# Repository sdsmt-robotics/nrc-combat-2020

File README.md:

# nrc-combat-2020
Robot code for the NRC Combat competition bot. Information about this bot can be found here: http://robotics.sdsmt.edu/projects/spinnybot  

# Hardware Info
This code is meant to run on an ESP32. It uses an ICM20649 Wide-Range 6-DoF IMU for orientation sensing. It also controls three NeoPixel 8x5050 RGB LED Sticks. For motor control, it interfaces with three Nidec24h motors controlled by our custom motor controller boards. For remote control, the bot receives commands from our custom remote controls over an xBee. The full system diagram is shown below.  

The main components of the control system (ESP32, xBee, voltage regulators, level shifters, etc) are held on a custom main board. The Kicad files for this are in the [spinnybot-motherboard](https://github.com/sdsmt-robotics/nrc-combat-2020/tree/master/spinnybot-motherboad) folder.  

# Software Info  
The main code for the bot is found in the [spinnybot-code](https://github.com/sdsmt-robotics/nrc-combat-2020/tree/master/spinnybot-code) folder. There are some additional arduino sketches for testing the various functionallities. These are found in the "testing" sub-folder. These tests run with the same libraries as the main control code.  

The pinouts are set up to run with the ESP32. But it should be able to run on any device with similar pin functionalities.  

## Required Libraries  
The required libraries are as follows:  
* Nidec24hController.h - Interface lib for the motor speed controller. Found [here](https://github.com/sdsmt-robotics/MotorSpeedController/tree/master/Software/controllerInterfaceLib).  
* Controller.h - Receive library for our custom remote control. Found [here](https://github.com/sdsmt-robotics/MotorSpeedController/tree/master/Software/controllerInterfaceLib).  
* FastLED.h - Code for interfacing with the LED strips. Install through the Arduino library manager.  
* Adafruit_ICM20649.h - Library for the ICM-20649 IMU. Install through the Arduino library manager.  

## Functionality  
The functionality is as follows. First, the bot will first initialize all peripherals. The LED strips are initialized first to show status throughout.Then the IMU is initialized. While this is occurring, the bot MUST remain stationary. The code runs through a calibration sequence each time, and any bumps will cause issues. During this stage the LEDs will show yellow, and will go green once complete. After, this the motors and remote control communications will be set up as well.  

For the main control loop, the bot has three main states:  
* No-spin: lights will be purple and the bot will not be spinning. Driver can drive the bot around with standard controls.  
* Spinny: bot is spinning with IMU feedback for orientation. LEDs will be red except when facing forward at which point they will be blue. Controls for driving are relative to "forward".  
* Full-spinny: lights will be red and bot will set all motors to full power. Feedback from IMU and attempts to drive will be ignored.

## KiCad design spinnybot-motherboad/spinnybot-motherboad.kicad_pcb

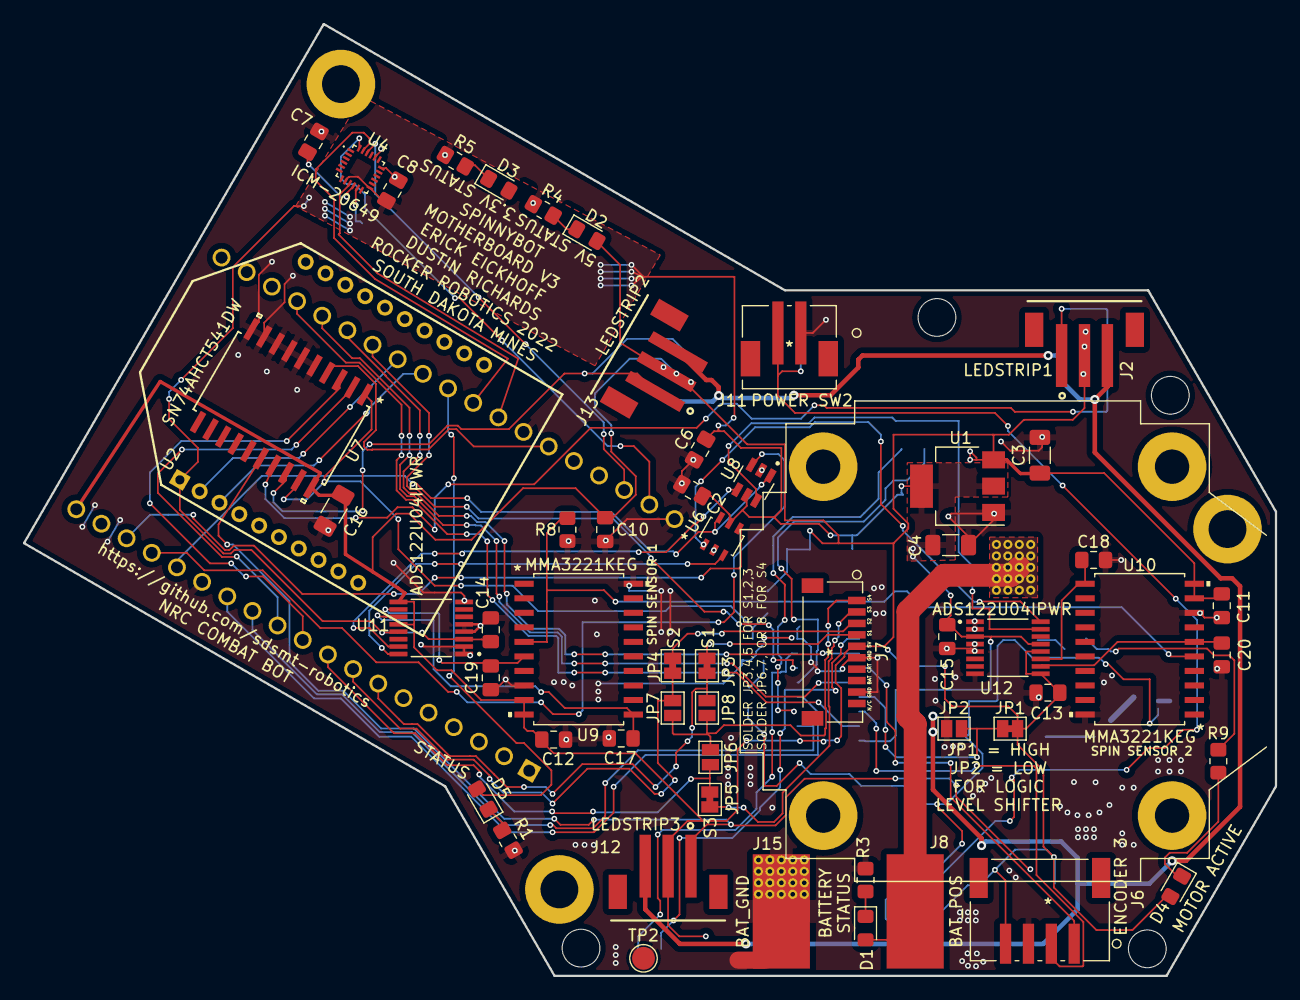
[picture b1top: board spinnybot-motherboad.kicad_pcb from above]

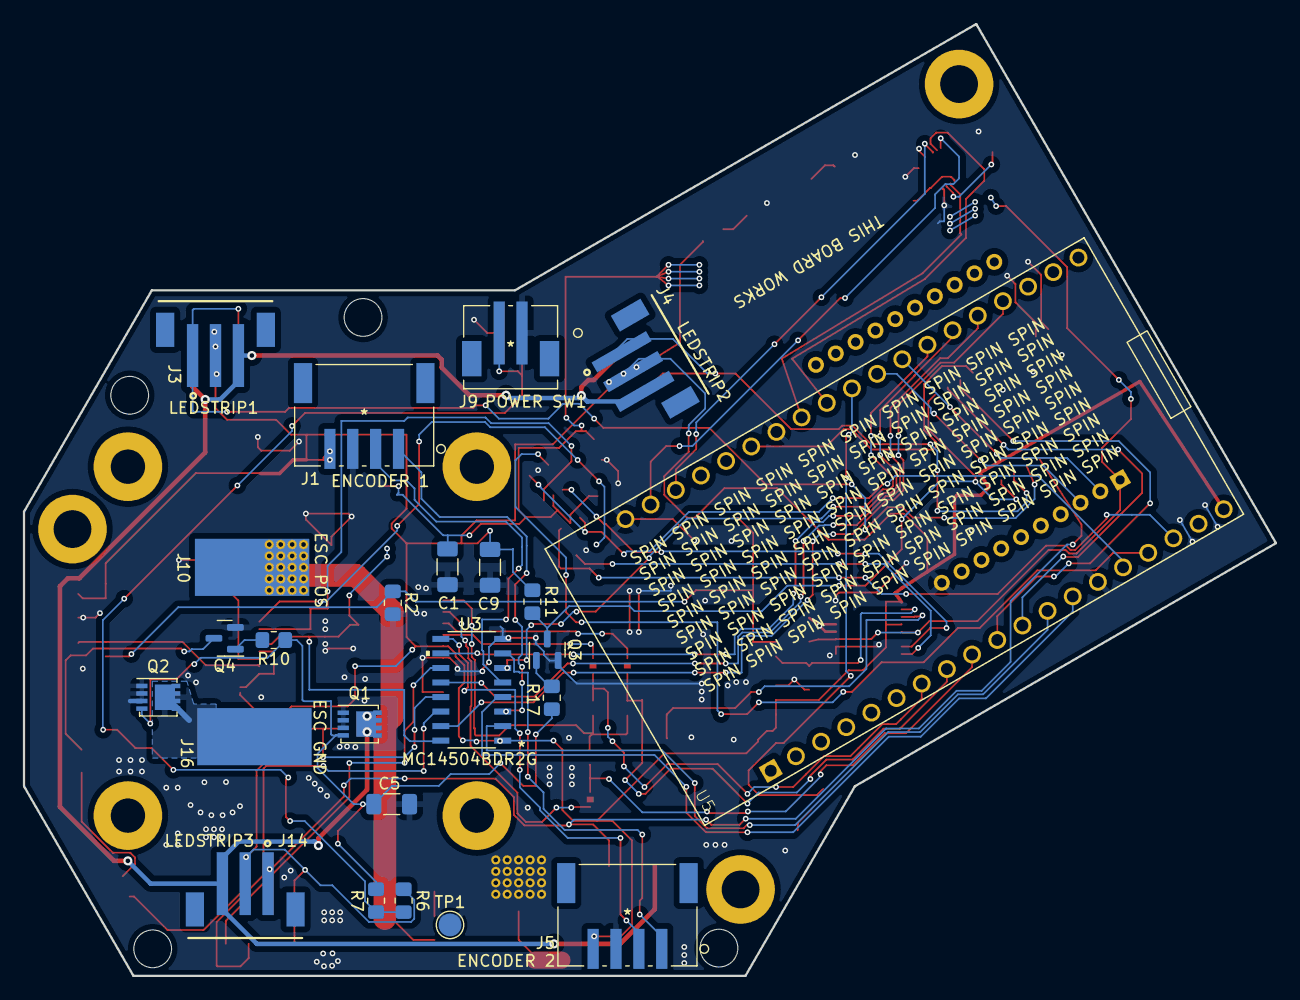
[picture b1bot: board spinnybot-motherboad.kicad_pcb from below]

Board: 2 copper layers, 109.4 x 83.2 mm, 87 parts (24 on the bottom side), 63 nets.

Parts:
A1: ESC_Hobbywing_X-Rotor_Micro_60A_4in1
C1, C3, C4, C5, C9: 10u; C_1206_3216Metric_Pad1.33x1.80mm_HandSolder
C2, C6, C7, C8, C10, C11, C12, C13, C14, C15: 0.1u; C_0805_2012Metric_Pad1.18x1.45mm_HandSolder
C16: 0.1u; C_1206_3216Metric_Pad1.33x1.80mm_HandSolder
C17, C18, C19, C20: 10nF; C_0805_2012Metric_Pad1.18x1.45mm_HandSolder
D1: 12V; LED_0805_2012Metric_Pad1.15x1.40mm_HandSolder
D2: 5V; LED_0805_2012Metric_Pad1.15x1.40mm_HandSolder
D3: 3V3; LED_0805_2012Metric_Pad1.15x1.40mm_HandSolder
D4: MOTOR ACTIVE; LED_0805_2012Metric_Pad1.15x1.40mm_HandSolder
D5: STATUS; LED_0805_2012Metric_Pad1.15x1.40mm_HandSolder
H1: MOUNTINGHOLE1; MountingHole_3.3mm
H2, H7: STRAINHOLE1; StrainHole_3.3mm
H3: MOUNTINGHOLE2; MountingHole_3.3mm
H4: MOUNTINGHOLE3; MountingHole_3.3mm
H6: STRAINHOLE3; StrainHole_3.3mm
H8: STRAINHOLE2; StrainHole_3.3mm
J1: ENCODER 1; S4B-PH-SM4-TBLFSN
J2, J3: LEDSTRIP1; JST_B3B-PH-SM4-TB(LF)(SN)
J4, J13: LEDSTRIP2; JST_B3B-PH-SM4-TB(LF)(SN)
J5: ENCODER 2; S4B-PH-SM4-TBLFSN
J6: ENCODER 3; S4B-PH-SM4-TBLFSN
J7: SM10B-SRSS-TB
J8: BAT_POS; SolderWirePad_1x01_SMD_5x10mm
J9: POWER SW1; B2B-PH-SM4-TBLFSN
J10: ESC_POS; Stitched_SolderWirePad_1x01_SMD_5x10mm
J11: POWER SW2; B2B-PH-SM4-TBLFSN
J12, J14: LEDSTRIP3; JST_B3B-PH-SM4-TB(LF)(SN)
J15: BAT_GND; Stitched_SolderWirePad_1x01_SMD_5x10mm
J16: ESC_GND; SolderWirePad_1x01_SMD_5x10mm
JP1, JP3, JP4, JP5: SolderJumper_2_Bridged; SolderJumper-2_P1.3mm_Bridged_Pad1.0x1.5mm
JP2, JP6, JP7, JP8: SolderJumper_2_Open; SolderJumper-2_P1.3mm_Open_Pad1.0x1.5mm
Q1, Q2: SISA96DN; Vishay_PowerPAK_1212-8_Single
Q3, Q4: BC846; SOT-23
R1, R5: 130; R_0805_2012Metric_Pad1.20x1.40mm_HandSolder
R2, R8: 10k; R_0805_2012Metric_Pad1.20x1.40mm_HandSolder
R3, R11: 1K; R_0805_2012Metric_Pad1.20x1.40mm_HandSolder
R4: 301; R_0805_2012Metric_Pad1.20x1.40mm_HandSolder
R6: 1k; R_0805_2012Metric_Pad1.20x1.40mm_HandSolder
R7: 150k; R_0805_2012Metric_Pad1.20x1.40mm_HandSolder
R9: 220; R_0805_2012Metric_Pad1.20x1.40mm_HandSolder
R10, R17: 10K; R_0805_2012Metric_Pad1.20x1.40mm_HandSolder
TP1, TP2: TestPoint; TestPoint_Pad_D2.0mm
U1: LM1117-3.3; SOT-223-3_TabPin2
U2: XBP9B-DMWTB002; DIP2200W51P200L3294H279Q20P
U3: MC14504BDR2G
U4: ICM-20649; QFN40P300X300X95-24N
U5: ESP32-DEVKITC-32D; MODULE_ESP32-DEVKITC-32D
U6: 74LVC1G157GV_125
U7: SN74AHCT541DW
U8: SN74LVC1G18DBVR; SOT95P280X145-6N
U9, U10: MMA3221KEG
U11, U12: ADS122U04IPWR; SOP65P640X120-16N

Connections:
+3V3: C1.1, C2.1, C4.1, C6.1, C8.1, C14.1, C15.1, D3.2 (A), U1.2 (VO), U2.1 (VCC), U3.16 (VDD), U4.8 (VDDIO), U4.13 (VDD), U6.5 (VCC), U8.5 (VCC), U11.3 (RESET_N), U11.13 (DVDD), U12.3 (RESET_N), U12.13 (DVDD)
+5V: C3.1, C9.1, C10.1, C11.1, C12.1, C13.1, C16.1, D2.2 (A), D4.2 (A), J1.4, J2.2, J3.2, J4.2, J5.4, J6.4, J7.5, J12.2, J13.2, J14.2, JP1.2 (B), R6.1, R11.1, U1.3 (VI), U3.1 (VCC), U5.19 (EXT_5V), U7.20 (VCC), U9.9 (VDD), U9.10 (AVDD), U10.9 (VDD), U10.10 (AVDD), U11.9 (REFP), U11.12 (AVDD), U12.9 (REFP), U12.12 (AVDD)
+12V: D1.2 (A), J8.1, J10.1
/ACCEL_SELF_TEST: R2.1, R8.1, U9.5 (ST), U10.5 (ST)
/ADC_RX: U5.17 (SD3), U6.4 (Y)
/ADC_SEL: U5.15 (IO13), U6.6 (S), U8.1 (S)
/ADC_TX: U5.16 (SD2), U8.3 (A)
/Connectors/ESC_S4: J7.1, JP6.1 (A), JP7.1 (A), JP8.1 (A)
/ENC_1A_5V: J1.1, U3.3 (AIN)
/ENC_1B_5V: J1.2, U3.5 (BIN)
/ENC_2A_5V: J5.1, U3.7 (CIN)
/ENC_2B_5V: J5.2, U3.9 (DIN)
/ENC_3A_5V: J6.1, U3.11 (EIN)
/ENC_3B_5V: J6.2, U3.14 (FIN)
/ESC_S1: JP3.2 (B), JP8.2 (B), U5.7 (IO32)
/ESC_S2: JP4.2 (B), JP7.2 (B), U5.8 (IO33)
/ESC_S3: JP5.2 (B), JP6.2 (B), U5.9 (IO25)
/IMU and Accelerometers/ADC1_RX: U6.3 (I0), U11.16 (RX)
/IMU and Accelerometers/ADC1_TX: U8.4 (Y1), U11.15 (TX)
/IMU and Accelerometers/ADC2_RX: U6.1 (I1), U12.16 (RX)
/IMU and Accelerometers/ADC2_TX: U8.6 (Y2), U12.15 (TX)
/IMU_CS: U4.22 (NCS), U5.22 (IO22)
/LEDSTRIP1_DATA_5V: J2.1, J3.1, U7.17 (Y2)
/LEDSTRIP2_DATA_5V: J4.1, J13.1, U7.18 (Y1)
/LEDSTRIP3_DATA_5V: J12.1, J14.1, U7.16 (Y3)
/LEDSTRIP_GND: J2.3, J3.3, J4.3, J12.3, J13.3, J14.3, Q1.5 (D)
/MCU and Buffers/BUFFER_OE: Q3.3 (C), R11.2, U7.1 (*OE1), U7.19 (*OE2)
/MCU and Buffers/ENC_1A_3V3: U3.2 (AOUT), U5.12 (IO14)
/MCU and Buffers/ENC_1B_3V3: U3.4 (BOUT), U5.13 (IO12)
/MCU and Buffers/ENC_2A_3V3: U3.6 (COUT), U5.32 (IO4)
/MCU and Buffers/ENC_2B_3V3: U3.10 (DOUT), U5.33 (IO0)
/MCU and Buffers/ENC_3A_3V3: U3.12 (EOUT), U5.34 (IO2)
/MCU and Buffers/ENC_3B_3V3: U3.15 (FOUT), U5.35 (IO15)
/MCU and Buffers/LEDSTRIP1_DATA_3V3: U5.10 (IO26), U7.3 (A2)
/MCU and Buffers/LEDSTRIP2_DATA_3V3: U5.11 (IO27), U7.2 (A1)
/MCU and Buffers/LEDSTRIP3_DATA_3V3: U5.25 (IO21), U7.4 (A3)
/MCU and Buffers/XBEE_RX: U2.3 (DIN/NCONFIG/DIO14), U5.30 (IO17)
/MCU and Buffers/XBEE_TX: U2.2 (DOUT/DIO13), U5.31 (IO16)
/MISO_3V3: U4.9 (AD0/SDO), U5.27 (IO19)
/MOSI_3V3: U4.24 (SDA/SDI), U5.21 (IO23)
/POWER_ON: C5.2, Q1.4 (G), Q2.4 (G), R7.2, R10.1, R17.2
/Power/ESC_GND: J16.1, Q2.5 (D)
/Power/POWER_SW_IN: J9.2, J11.2, R6.2, R7.1
/SCK_3V3: U4.23 (SCL/SCLK), U5.28 (IO18)
GND: C1.2, C2.2, C3.2, C4.2, C5.1, C6.2, C7.2, C8.2, C9.2, C10.2, C11.2, C12.2, C13.2, C14.2, C15.2, C16.2, C17.2, C18.1, C19.1, C20.1, J1.3, J5.3, J6.3, J7.6, J7.9, J9.1, J11.1, J15.1, JP2.1 (A), Q1.1 (S), Q1.2 (S), Q1.3 (S), Q2.1 (S), Q2.2 (S), Q2.3 (S), Q3.2 (E), Q4.2 (E), R1.1, R2.2, R3.1, R4.1, R5.1, R8.2, TP1.1, TP2.1, U1.1 (GND), U2.10 (GND), U3.8 (VSS), U4.11 (FSYNC), U4.18 (GND), U4.20 (RESV), U5.14 (GND1), U5.20 (GND3), U5.26 (GND2), U6.2 (GND), U7.5 (A4), U7.6 (A5), U7.7 (A6), U7.8 (A7), U7.9 (A8), U7.10 (GND), U8.2 (GND), U9.8 (VSS), U9.20 (GND), U10.8 (VSS), U10.20 (GND), U11.1 (GPIO1), U11.2 (GPIOO), U11.4 (DGND), U11.5 (AVSS), U11.8 (REFN), U12.1 (GPIO1), U12.2 (GPIOO), U12.4 (DGND), U12.5 (AVSS), U12.8 (REFN)
unnamed: C7.1, U4.10 (REGOUT)
unnamed: C17.1, U9.11 (YOUT), U11.11 (AINO)
unnamed: C18.2, U10.11 (YOUT), U12.11 (AINO)
unnamed: C19.2, U9.6 (XOUT), U11.10 (AIN1)
unnamed: C20.2, U10.6 (XOUT), U12.10 (AIN1)
unnamed: D1.1 (K), R3.2
unnamed: D2.1 (K), R4.2
unnamed: D3.1 (K), R5.2
unnamed: D4.1 (K), R9.2
unnamed: D5.1 (K), R1.2
unnamed: D5.2 (A), U5.29 (IO5)
unnamed: J7.2, JP5.1 (A)
unnamed: J7.3, JP4.1 (A)
unnamed: J7.4, JP3.1 (A)
unnamed: JP1.1 (A), JP2.2 (B), U3.13 (MODE)
unnamed: Q3.1 (B), R17.1
unnamed: Q4.1 (B), R10.2
unnamed: Q4.3 (C), R9.1

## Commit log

2019-11-02 added some starting code
2019-11-02 added some imu code code, currently commented out
2019-11-09 changed drive code to use the rotation matrix, works for the most part
2020-01-08 Add Sparkfun Razor Imu example code
2020-01-11 Update the readme
2020-02-08 Switched the motor object over to the new motor driver and commented out IMU code
2020-02-09 Fixed motor objects.
2020-02-15 Fixed kiwi drive for new motor controllers.
2020-02-16 Added the "slave" files for offloading the motor encoder processing to a "slave" Arduino.
2020-02-22 Added changes to kiwi drive and the example i2c master code.
2020-02-22 Replaced the library files for the speedController library
2020-02-22 Consolodated the slave and master motor controller code
2020-02-22 Add motor control example files
2020-02-22 Add readme for motor speed controller code
2020-02-22 PID now works for forward and backward motor motion.
2020-02-23 Re-added the full PID.
2020-02-23 Create ATTiny84aExample
2020-02-23 Update ATTiny84aExample
2020-02-24 Add class for the Nidec motor
2020-02-26 Split some things out into classes and add some test modes
2020-02-26 Move the speed control stuff into a seperate class
2020-02-26 updated kiwi drive code
2020-02-27 Add motor info to readme
2020-02-29 updated code to add safety systems for loss of communication.
2020-02-29 Added missing else-statement
2020-02-29 Fine tuned values
2020-02-29 test
2020-03-01 updated code.
2020-03-07 updated code to be more efficient. Improved magnetometer filtering.
2020-03-10 Make compatible with ATtiny and change to using a Kalman filter
2021-01-24 Added Motor controller submodule
2021-01-29 first commit of 2021
2021-02-14 Deleted old and unnecessary code code for old hardware and added the new IMU and LED code.
2021-02-14 Removed unnecessary code and libraries from the old kiwi-drive code. The new IMU and LED code will be moved to this file. In addition, the code will be modified to use sams motor controller library a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
2021-02-15 Updated the code to remove the unnecessary exponential filter
2021-02-15 Added the IMU and LED code
2021-02-15 Implemented the Nidec24hController class. Testing still needs to be completed.
2021-02-17 Added the xBee controller receive code to replace the PS3 code used for testing.
2021-02-18 Cleaned up the code and added additional documentation.
2021-02-20 Made some minor changes to the final code based on debugging results.
2021-02-21 Started to move the POV display class into its own library to help with future development. (DOES NOT COMPILE)
2021-02-26 Fixed the POV_desplay class so that it both compiles and the number of leds can be easily changed. Some rework needs to be done for the screen class to be safe to use in the final application, i.e. p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
2021-02-27 Made some changes to how stripe was being utilized and moved some of its functionality to the screen class to hopefully reduce the amount of dynamic memory allocation that is required.
2021-03-17 Make changes to code to work with test chassis
2021-03-18 Combined modifications resulting from testing with improvements made to increase code efficiency.
2021-03-19 Separated the IMU code out into its own class and simplified the main drive code accordingly.
2021-03-19 Fixed several bugs related to the implementation (Temporarily removed POV display code).
2021-03-20 Added the simple Kalman filter to the BB_IMU code. Added an modifiable offset to the BB_IMU code and made the relevant changes in the kiwi drive code. Cleaned up the kiwi drive code.
2021-03-24 Made small updates to values
2021-03-27 Added a low pass filter into the bb imu class.
2021-03-27 Added improvements to calculate the values necessary for rotation and translation speeds.
2021-03-27 fixed bug in the code because apparently semicolons are important.
2021-03-28 Added the ability to speed up or slow down the bot based on the controller state. This amplification is currently set at +- 50%.
2021-03-30 Updated the code to use multiple strips of leds
2021-03-30 Split the controller updates and motor speed calculations off into separate functions.
2021-03-30 Added bb upright detection to the IMU code and implemented the upright detection into the main drive code.
2021-03-31 Made some minor changes to the led code.
2021-04-01 Made insignificant changes.
2021-04-01 Add intermediate changes for final code
2021-04-10 add kicad files for mainboard
2021-04-10 pcb layout
    updated the pcb circuit diagram with some changes in parts etc.
2021-04-11 worked on redesigning the pcb design for the new shape
2021-04-17 small edits to the motherboard schematic
2021-04-24 Add tweaks to get running
2021-04-27 board rev 2, got all components placed. still need to route
2021-04-29 routed rev2 mainboard
2021-04-29 added graphics and generated gerbers
2021-05-01 Implement new IMU and do some code cleanup
2021-05-01 Minor bug fixes
2021-05-01 Updated the code to use the new IMU (This code has not been debuged or tested on the hardware so there are probably tons of problems).
2021-05-01 Fixed pin assignment.
2021-05-08 added PDF schematic and fixed a routing error
2021-05-12 Add changes from competition
2021-05-12 Reorganize and rename files
2021-05-12 Fix issue with missing library
2021-05-12 Fix missing image in readme
2021-11-18 Replaced transistor symbols and footprints with correct ones.
2022-02-06 split schematic into multiple files and stole Erick's homework on redoing the power button
2022-02-06 fixed some reference designators so the layout isn't broken
2022-02-10 Changed values for power RC circuit
2022-02-17 Removed buck converter PS1, voltage sense divider, and motor connections. Added encoder connectors
2022-02-19 Added ESC connections
2022-02-26 Made and imported ESC footprint, added 10 pin JST connector symbol and footprint, updated Q2 FET to control ESC power
2022-02-27 add accelerometers, ADCs, and UART multiplexer
2022-02-27 Libraries for esc and 10 pin connector
2022-02-27 fix broken file after merge
2022-02-27 cleaning up temporary files from repo
2022-02-27 more temp file cleanup
2022-03-03 removed some old signals
2022-03-03 Made ESP32 connections, added logic level shifter
2022-03-05 PCB schematic (hopefully) finished
2022-03-05 Added 4 pin JST connector footprint and assigned footprints
2022-03-06 Started board layout
2022-03-08 Continued adding to board layout, added missing ESC connector footprint
2022-03-09 Most of the parts on the board, still missing battery connections
2022-03-10 Power pads added, beginning routing
2022-03-10 initial upload of new code for 2022
2022-03-11 Finishing routing board, needs checking over to make sure everything looks good
2022-03-11 Added chip names and solder jumper instructions
2022-03-12 Addressed Pratik's concerns about cap placement and missing caps
2022-03-12 PCB design rule checker fixes, silkscreen overlaps and self-intersecting courtyards
2022-03-12 fix LEDSTRIP_GND on the FET not being connected
2022-03-13 tweaks to routing to make the ground plane more connected, add a top copper ground pour. move ESC FET.
2022-03-13 add a couple ground test points
2022-03-13 swap out motor active indicator FET for a BJT we already have
2022-03-13 add more no-connect flags to schematic
2022-03-13 adjust mounting holes to have pads and change locations
2022-03-13 silkscreen fix, add 'THIS BOARD WORKS'
2022-03-13 change solder mask to purple
2022-03-13 add 3d models, silkscreen fixes
2022-03-13 move encoder cable strain relief holes
2022-03-13 DRC fixes
2022-03-13 move ESC FET
2022-03-14 add extra strain relief holes back in the original locations
2022-03-14 update 3d model
2022-03-14 adjust board to use new outline with bottom edge closer to center
2022-03-14 add new 3d model
2022-03-24 added some adc stuff, untested
2022-03-28 untested half working code esp32 boots now
2022-03-28 possibly fix leds untested
2022-03-29 aaaaaaaaaaaaahhhhhhhhhhhhh
2022-03-29 confirmed serial1 pin swap worked
2022-03-29 Generated step file for insert team
2022-03-30 pins remap leds work gyro i2c now
2022-03-31 Created branch for ADC test code
2022-03-31 singing motors are always better
2022-03-31 improved documentation
2022-04-01 encoders work now
2022-04-01 got basic communication working with ADCs, code is a massive mess
2022-04-01 this really really sucks
2022-04-02 added an IMU offset to allow turning
2022-04-02 IMU communication working
2022-04-03 Do a slight project restructure and add IMU testing
    Created some PIO configs to make testing easier and added a test build target for the IMU.
2022-04-03 Add LED test code
2022-04-03 Add test for controller connection
2022-04-04 Add encoder test code and fix some bugs
2022-04-04 Add example motor control code
2022-04-05 Improve reliability of IMU angle tracking
2022-04-05 Make main file use shared pins.h and output stuff on startup
2022-04-05 Clean up testing code from ADC branch
2022-04-05 added some of sams code
2022-04-05 fixed imu code
2022-04-05 Updated voltage divider on power circuit
2022-04-06 added left slick button rearms motors
2022-04-06 fix build errors
2022-04-06 cleanup
2022-04-06 broken drive code
2022-04-06 Add OTA update example and functions
2022-04-07 setup for working on the adc_accelerometer_test example
2022-04-07 Fix drive code (hopefully)
2022-04-07 Add OTA updating
2022-04-07 changed motor init time to 2 seconds
2022-04-07 removed sams hardcoded spins
2022-04-07 deleted filter class and improved organization
2022-04-08 Add some improved angle tracking and drive code using encoder
2022-04-08 competition setup as of 4/8/22 at 8:50am
2022-04-09 added reed switch interupt to disable robot
2022-04-09 4/9/22 at 11:05 EST NRC

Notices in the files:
parts and their libraries:
Copyright 2021 Accelerated Designs. All rights reserved.
Copyright 2016 Accelerated Designs. All rights reserved.
